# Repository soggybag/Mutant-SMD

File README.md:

# Mutant SMD

A redesign of the **Mutant generative synth** (MeeBleeps, https://github.com/Meebleeps/MeeBleeps-Mutant-Synth), based on the Eurorack version in `~/Documents/Arduino/projects/Mutant_Generative_Arduino_Synth/` (Instructables "Mutant Generative Arduino Synth").

**Goals:**
- **One board, three uses:** bare, behind a Eurorack panel, or in an enclosure.
- **Board ≤ 100 mm** (the original is 65.3 × 106.4 mm), for JLC's price break.
- **SMD parts** for JLC assembly; panel parts hand-soldered.
- **Tayda A-8796 round buttons** (as on GlitchStorm v3).
- **Same control positions** as the original, so its front panel still fits.
- No front panel design for now.

**Status:** schematic + PCB v1.0, routed, DRC 0, parity clean, JLC files in production/. 2026-10-19: matrix supply filter added (R8 2.2 Ω + C16 100µ tantalum → V5M), re-routed. Not ordered yet.

- Schematic: [docs/MutantSMD_schematic.pdf](docs/MutantSMD_schematic.pdf), generated by `scripts/build_mutant.py`.
- Notes: [docs/Design Notes.md](docs/Design%20Notes.md).
- Firmware: the original `Mutant_Updated` (Mozzi 2) runs unchanged; the pin map is identical.

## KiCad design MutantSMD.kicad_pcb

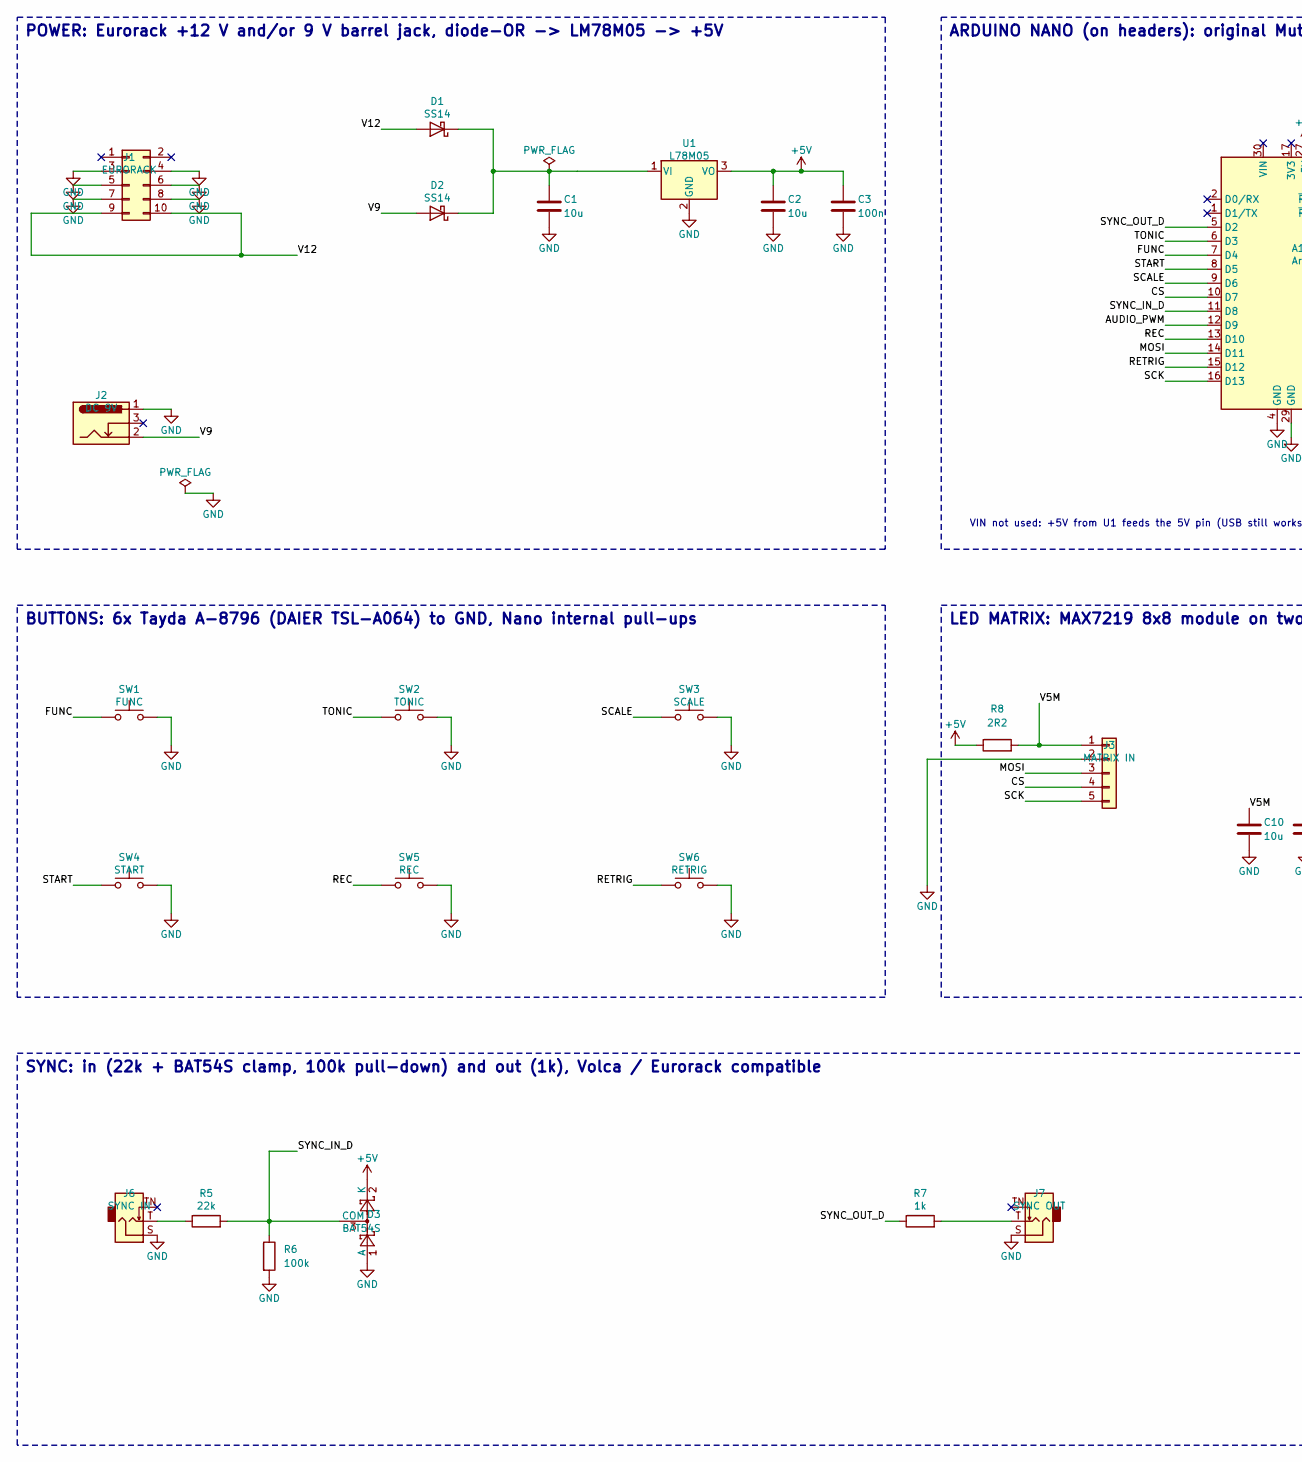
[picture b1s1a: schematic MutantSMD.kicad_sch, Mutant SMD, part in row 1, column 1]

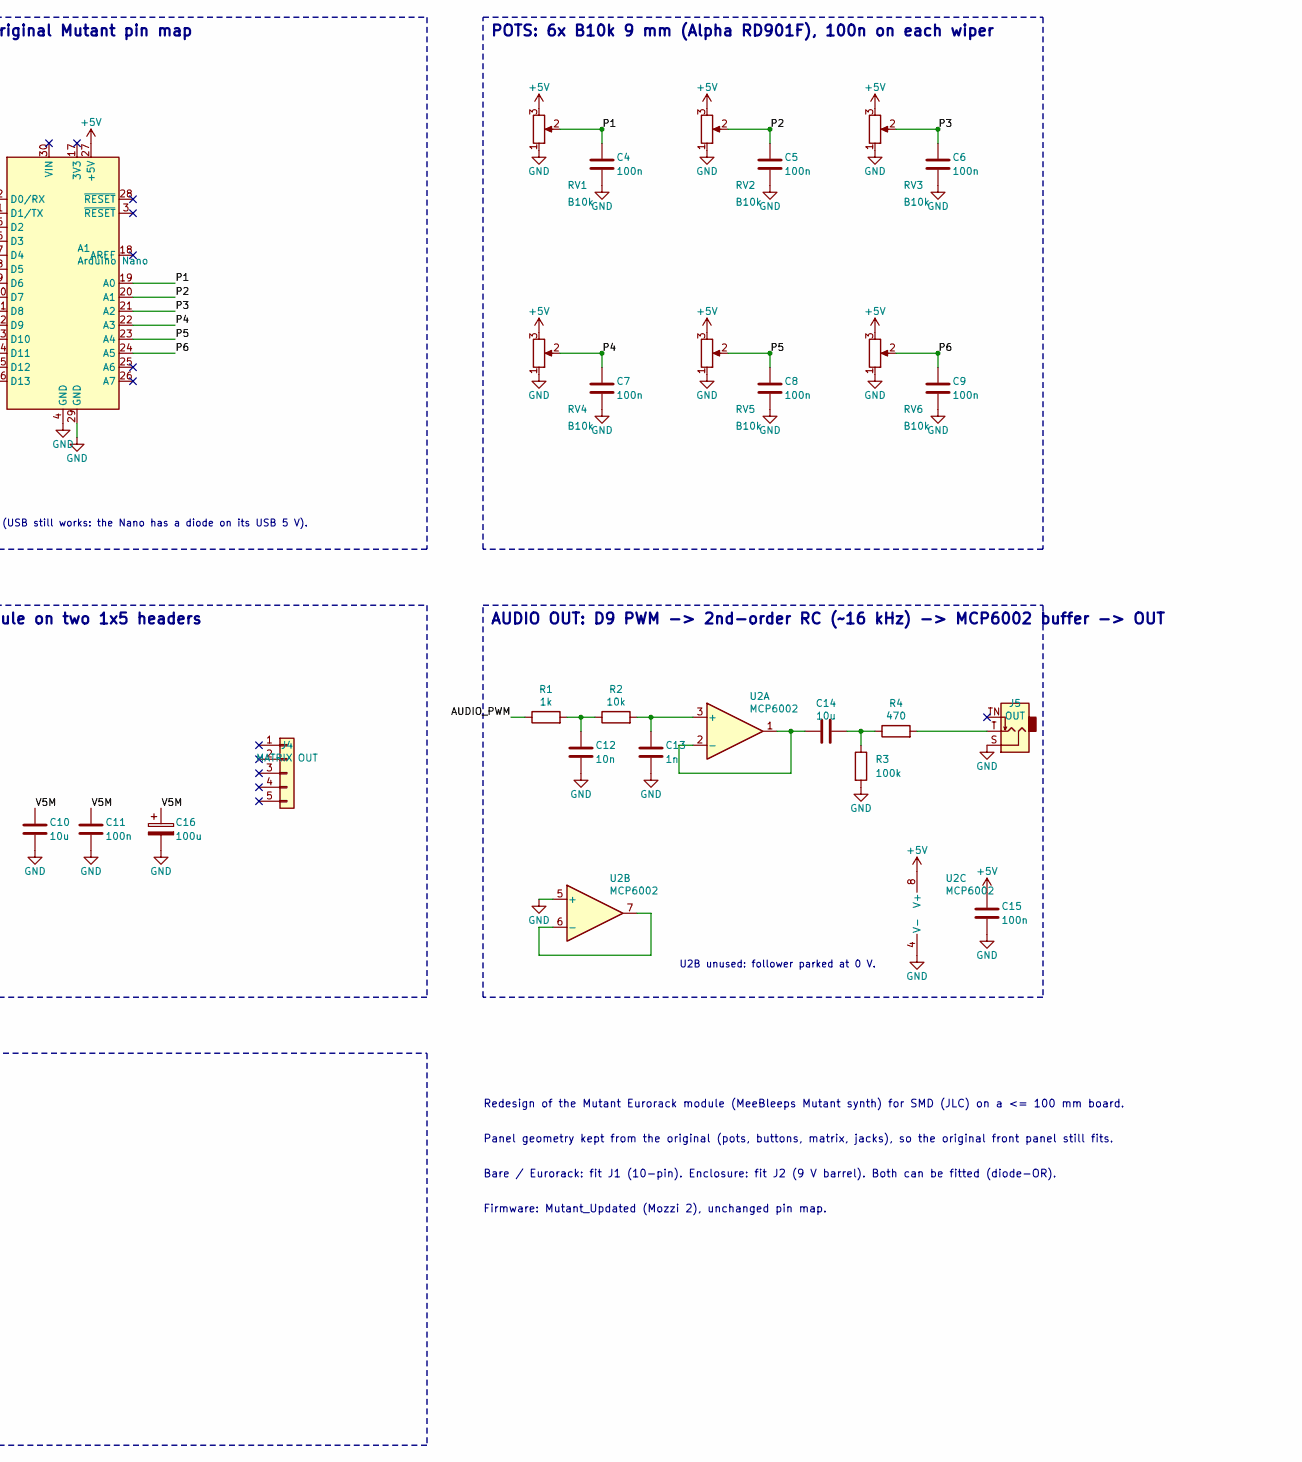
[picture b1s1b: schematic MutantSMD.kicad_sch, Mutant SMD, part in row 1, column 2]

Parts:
A1: Arduino Nano; Arduino_Nano
C1, C2, C10, C14: 10u; C_1206_3216Metric; LCSC C13585
C3, C4, C5, C6, C7, C8, C9, C11, C15: 100n; C_0805_2012Metric; LCSC C49678
C12: 10n; C_0805_2012Metric; LCSC C1710
C13: 1n; C_0805_2012Metric; LCSC C46653
C16: 100u; CP_EIA-3528-21_Kemet-B; LCSC C122271
D1, D2: SS14; D_SMA; LCSC C2480
D3: BAT54S; SOT-23; LCSC C19726
J1: EURORACK; IDC-Header_2x05_P2.54mm_Vertical
J2: DC 9V; BarrelJack_Horizontal
J3: MATRIX IN; PinSocket_1x05_P2.54mm_Vertical
J4: MATRIX OUT; PinSocket_1x05_P2.54mm_Vertical
J5: OUT; Jack_3.5mm_QingPu_WQP-PJ398SM_Vertical_CircularHoles
J6: SYNC IN; Jack_3.5mm_QingPu_WQP-PJ398SM_Vertical_CircularHoles
J7: SYNC OUT; Jack_3.5mm_QingPu_WQP-PJ398SM_Vertical_CircularHoles
R1, R7: 1k; R_0805_2012Metric; LCSC C17513
R2: 10k; R_0805_2012Metric; LCSC C17414
R3, R6: 100k; R_0805_2012Metric; LCSC C149504
R4: 470; R_0805_2012Metric; LCSC C17710
R5: 22k; R_0805_2012Metric; LCSC C17560
R8: 2R2; R_1206_3216Metric; LCSC C25369
RV1, RV2, RV3, RV4, RV5, RV6: B10k; Potentiometer_Alpha_RD901F-40-00D_Single_Vertical
SW1: FUNC; SW_Push_Round_D12mm_P5.00mm_DAIER_TSL-A064
SW2: TONIC; SW_Push_Round_D12mm_P5.00mm_DAIER_TSL-A064
SW3: SCALE; SW_Push_Round_D12mm_P5.00mm_DAIER_TSL-A064
SW4: START; SW_Push_Round_D12mm_P5.00mm_DAIER_TSL-A064
SW5: REC; SW_Push_Round_D12mm_P5.00mm_DAIER_TSL-A064
SW6: RETRIG; SW_Push_Round_D12mm_P5.00mm_DAIER_TSL-A064
U1: L78M05; TO-252-2; LCSC C58069
U2: MCP6002; SOIC-8_3.9x4.9mm_P1.27mm; LCSC C7377

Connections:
+5V: A1.27 (+5V), C2.1, C3.1, C15.1, D3.2 (K), R8.1, RV1.3, RV2.3, RV3.3, RV4.3, RV5.3, RV6.3, U1.3 (VO), U2.8 (V+)
/AUDIO_PWM: A1.12 (D9), R1.1
/CS: A1.10 (D7), J3.4
/FUNC: A1.7 (D4), SW1.1
/MOSI: A1.14 (D11), J3.3
/P1: A1.19 (A0), C4.1, RV1.2
/P2: A1.20 (A1), C5.1, RV2.2
/P3: A1.21 (A2), C6.1, RV3.2
/P4: A1.22 (A3), C7.1, RV4.2
/P5: A1.23 (A4), C8.1, RV5.2
/P6: A1.24 (A5), C9.1, RV6.2
/REC: A1.13 (D10), SW5.1
/RETRIG: A1.15 (D12), SW6.1
/SCALE: A1.9 (D6), SW3.1
/SCK: A1.16 (D13), J3.5
/START: A1.8 (D5), SW4.1
/SYNC_IN_D: A1.11 (D8), D3.3 (COM), R5.2, R6.1
/SYNC_OUT_D: A1.5 (D2), R7.1
/TONIC: A1.6 (D3), SW2.1
/V5M: C10.1, C11.1, C16.1, J3.1, R8.2
/V9: D2.2 (A), J2.2
/V12: D1.2 (A), J1.9, J1.10
unnamed: C12.1, R1.2, R2.1
unnamed: C14.2, R3.1, R4.1
unnamed: J5.T, R4.2
unnamed: J6.T, R5.1
unnamed: J7.T, R7.2
unnamed: C13.1, R2.2, U2.3 (+)
unnamed: C14.1, U2.1, U2.2 (-)
unnamed: U2.6 (-), U2.7

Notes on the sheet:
POWER: Eurorack +12 V and/or 9 V barrel jack, diode-OR -> LM78M05 -> +5V
ARDUINO NANO (on headers): original Mutant pin map
VIN not used: +5V from U1 feeds the 5V pin (USB still works: the Nano has a diode on its USB 5 V).
POTS: 6x B10k 9 mm (Alpha RD901F), 100n on each wiper
BUTTONS: 6x Tayda A-8796 (DAIER TSL-A064) to GND, Nano internal pull-ups
LED MATRIX: MAX7219 8x8 module on two 1x5 headers
AUDIO OUT: D9 PWM -> 2nd-order RC (~16 kHz) -> MCP6002 buffer -> OUT
U2B unused: follower parked at 0 V.
SYNC: in (22k + BAT54S clamp, 100k pull-down) and out (1k), Volca / Eurorack compatible
Redesign of the Mutant Eurorack module (MeeBleeps Mutant synth) for SMD (JLC) on a <= 100 mm board.
Panel geometry kept from the original (pots, buttons, matrix, jacks), so the original front panel still fits.
Bare / Eurorack: fit J1 (10-pin). Enclosure: fit J2 (9 V barrel). Both can be fitted (diode-OR).
Firmware: Mutant_Updated (Mozzi 2), unchanged pin map.

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
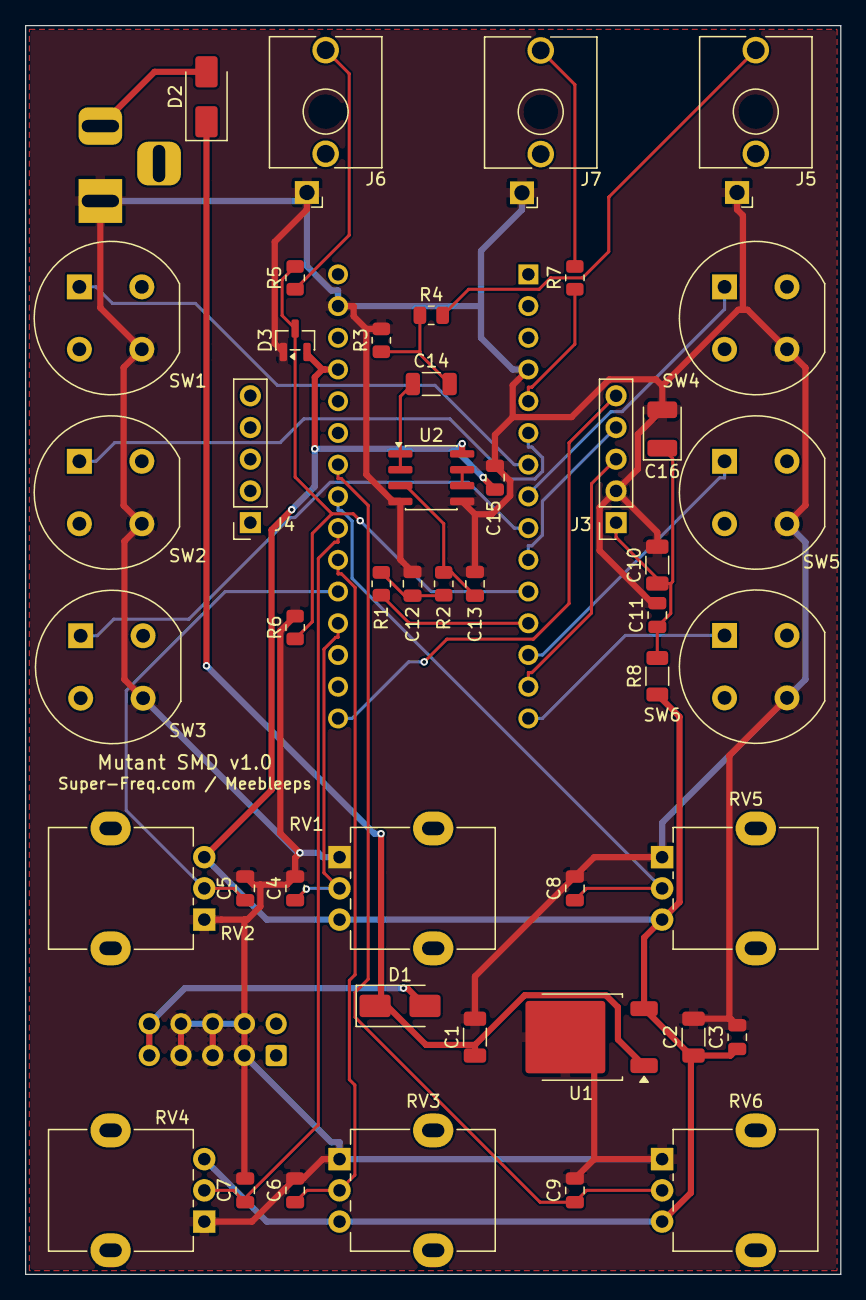
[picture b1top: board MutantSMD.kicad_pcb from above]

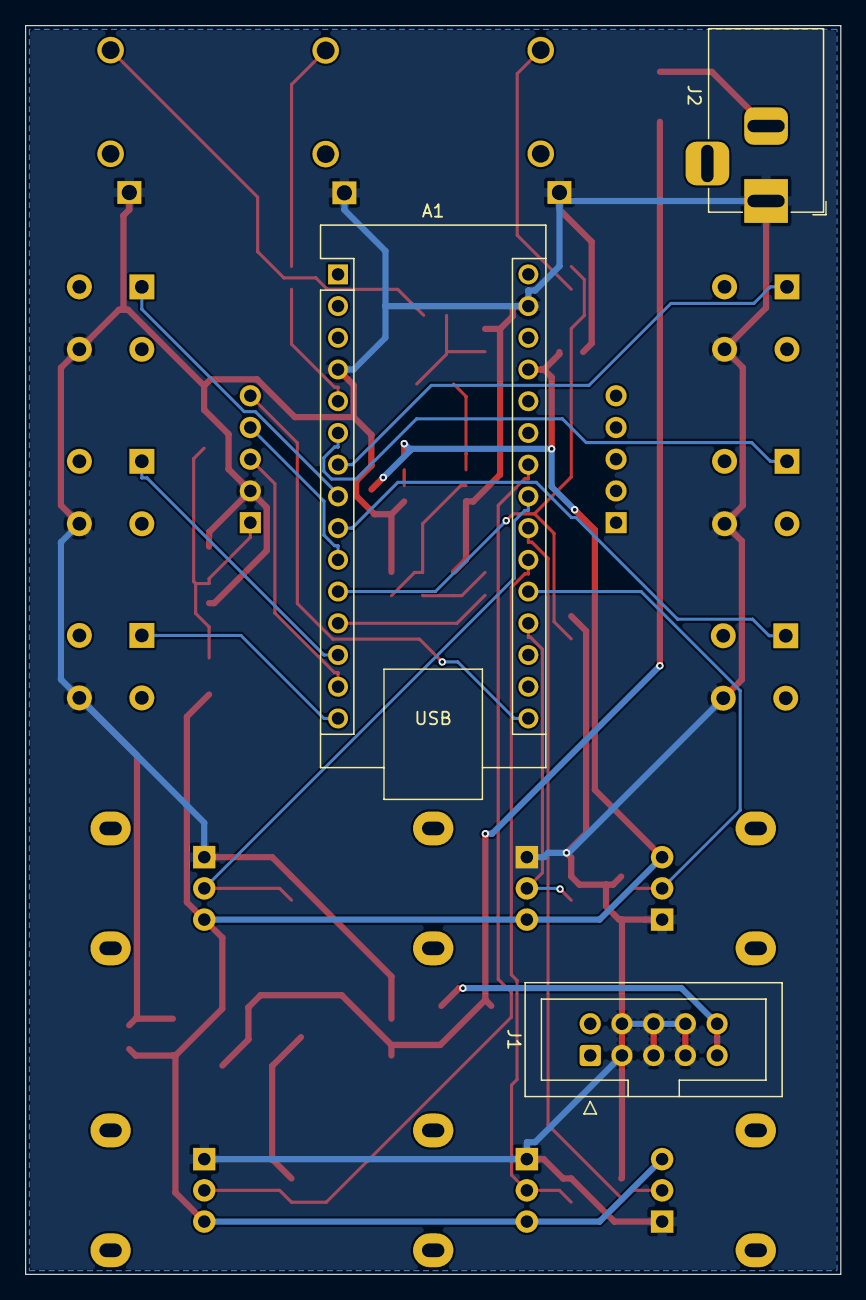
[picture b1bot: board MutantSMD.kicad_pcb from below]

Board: 2 copper layers, 65.3 x 100.0 mm, 49 parts (3 on the bottom side), 32 nets.
